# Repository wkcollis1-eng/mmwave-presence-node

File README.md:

<div align="center">

# mmWave Presence Lighting Node

**24 GHz Radar Presence Sensing for Room Lighting**

</div>

A 24 GHz radar presence sensor that turns a room's lamps on when someone walks in
and off some minutes after they leave — including for a person sitting still, in
the dark, reading, whom a PIR sensor cannot see.

An **HLK-LD2410C** radar and an **Adafruit VEML7700** light sensor on a **Seeed XIAO
ESP32-C3** carrier board, running **ESPHome**, with the control logic in **Home
Assistant**.

---

## The problem this is built for

> It is 23:00. The family room is dark and empty. A person walks in and sits down
> to read. The light comes on within one second, stays on for the next ninety
> minutes while they barely move, and goes off some minutes after they leave.
> Nobody touches a switch. Nobody is available to fix anything.

That is the acceptance test, not "99.9% uptime". A node that is powered and online
but drops the still-target at minute forty has failed the moment of demand — and so
has one that takes three seconds to notice someone walked in. The reasoning behind
every threshold, and the measurements that set them, are in
**[docs/mmwave-presence-node-design.md](docs/mmwave-presence-node-design.md)**.

## Status

| | |
|---|---|
| Design document | **Rev 1.11**, October 2026 |
| PCB | **Fabricated and populated.** 44.0 × 33.0 mm, 2-layer, three built |
| Bench validation | First session against real hardware **2026-09-07** — seven corrections and one retraction folded back into Rev 1.6. **14.5 days of bench data reviewed 2026-09-22** — folded into Rev 1.7 |
| Firmware / HA config | **Deployed.** Both nodes run firmware 0.4. The whole package (office and family room) is live in Home Assistant, derived from `packages/mmwave_presence.yaml` |
| Deployment | **Office live since 2026-09-26, family room since 2026-10-02.** First production review 2026-10-16, folded into Rev 1.8. A lamp lit into an empty room goes off after 5 min, from Rev 1.9 (2026-10-16). Family lamps the package lit go off on a bright morning, sunrise to noon, from Rev 1.10 (2026-10-19). Family lamps hold while the TV is on, from Rev 1.11 (2026-10-23) |
| Latency (R2) | **Family room: median 0.386 s, P95 0.409 s, n=103** [M] (HA's timestamps, presence edge → lamp relay on; not photons). **Office: median 2.404 s, P95 6.769 s, n=68** [M]. That is not met by design: the office lamp waits until the person is inside the approach limit, so a walk from the doorway is in the figure. Before that filter it was median 0.387 s, n=25 [M] — design doc §8 |
| Known fault | **The office node loses power every night**, about 23:30 to 07:00 [M: 13 nights, 09-29 → 10-12], and was dark for 79.66 h on 10-12 → 10-15 [M]. Under the §7 "lamp stays on while the node is offline" rule, the lamp stayed lit through 6 of those nights, 47.06 h in all [M]. Cause (owner, 2026-10-16): the node's outlet strip is fed by the Kasa computer outlet, which goes off overnight; the outlet's off-spans match all 14 dark gaps [M]. The remedy is the owner's call — design doc §9 item 16 |

The design document's §0 recorded what was its most consequential open question:
**the 5.6 m detection target and the gate-2 (7.4 ft) cap needed to reject a person
in the next room cannot both hold.** It is closed (owner-confirmed 2026-10-23), and
neither is kept for the office. The 5.6 m target is a family-room requirement only
(design doc §3.6); that node runs max gate 8. The office rejects the bathroom next
door in Home Assistant instead: occupancy starts only on a target reported inside
82 in (owner, 2026-10-16), live since 2026-09-27 as the P24 filter in
`packages/mmwave_presence.yaml`. A gate-2 cap was rejected because the doorway
reads at gate 3 too, so it would read a person standing there as empty. The office
radar still runs placeholder gates (move 4, still 4) until they are measured at the
mount (design doc §9 item 11).

## Repository layout

```
docs/          Design document, draft notes, the LD2410C documentation review,
               and the Hi-Link / Adafruit primary sources they cite
hardware/      KiCad 10 board, 3D models, gerbers, enclosure DXF, BOM
esphome/       Node firmware — common config plus per-node overlays
packages/      Home Assistant package: the control logic and its helpers
dashboards/    Home Assistant views for commissioning and monitoring
scripts/       Calibration and config-checking tools
assets/        Photos of the built node
```

`esphome/`, `packages/`, `dashboards/` and `scripts/` deliberately mirror the
layout under Home Assistant's `/config`, so a path named in the notes means the
same thing here and on the target.

## Hardware

| | |
|---|---|
| Board | 44.0 × 33.0 mm, 2-layer, 1 oz copper, 1.6 mm FR4 |
| Front copper | Pads and vias only, no traces — unbroken ground plane under the radar |
| Back copper | All routing. 1 mm power, 0.25 mm signal, 0.2 mm clearance |
| Mounting | 3 × M3 NPTH; H2 and H3 sit under U2's courtyard by design — use nylon fasteners |
| Vias | 67 total, 16 under the module, largest gap 5.39 mm (below λg = 5.96 mm) |

**1 oz / 1.6 mm, not 2 oz / 0.8 mm.** At 24.125 GHz the skin depth is 0.425 µm, so
1 oz is already 82 skin depths and 2 oz buys nothing electrically. 0.8 mm has 1/8
the flexural rigidity, which is the wrong direction for a vertically mounted board
carrying a cantilevered radar where flex changes the antenna-to-window distance.

### Radar interconnect

Module pin order, printed on the antenna face: **TX RX OUT GND VCC**.

| LD2410C | Signal | Direction | XIAO | GPIO |
|---|---|---|---|---|
| 1 | UART_Tx | module → ESP | D3 | GPIO5 |
| 2 | UART_Rx | ESP → module | D2 | GPIO4 |
| 3 | OUT | module → ESP | D10 | GPIO10 (via R1) |
| 4 | GND | — | GND | — |
| 5 | VCC | 5 V in | **VBUS**, not 3V3 | — |

> **Identify every pin by its silkscreen label, never by position or number.**
> VCC and TX sit at opposite ends of a five-pin header, so counting from the wrong
> end puts 5 V on TX. That is the one wiring error on this module that destroys
> something.

### PH1 — light sensor header

| pad | label | XIAO | GPIO |
|---|---|---|---|
| 1 | 3V3 (RED) | 3V3 | — |
| 2 | GND (BLACK) | GND | — |
| 3 | SCL (YELLOW) | D5 | GPIO7 |
| 4 | SDA (BLUE) | D4 | GPIO6 |

The colours match the Qwiic/STEMMA QT convention. **The pin order deliberately does
not** — it was chosen for cleaner routing, and the silkscreen colour labels are the
interface instead.

> ### Build constraint: only a flying-lead QT cable works
>
> Adafruit **4397** terminates in four independent female sockets, so each wire is
> placed by colour. **A molded 4-pin housing cable connects power backwards and
> destroys the sensor.** The board tells you the colours but not why.

**Cut the VEML7700's power-LED jumper before the sensor goes near the enclosure.**
The Adafruit 4162 carries a green power LED on the same face as the photodiode.
This is a sealed box: an ambient-light sensor locked in the dark with its own light
source is partly measuring that source, and because the offset is constant it
presents as a calibration rather than a fault.

**The light sensor is off-board on a 150 mm cable, by design.** On-carrier it sat
3.41 mm from the module edge — a near-field problem — and it could not be aimed
independently of the radar.

## Working on the board

Open `hardware/mmWave Presence Lighting Node.kicad_pro` in **KiCad 10**. All in-repo
3D models resolve through `${KIPRJMOD}/3d/`, so a fresh clone renders the full
assembly with no path fixing.

Two things to know before you file a bug against the board:

1. **There is no schematic.** The project is board-only, so KiCad cannot run
   connectivity or clearance DRC against a netlist — every error across seven
   revisions was found by reading coordinates. Building the schematic is open item
   §9.5 and is the one gate still running on human attention.
   *Corrected 2026-09-22: too strong. The pads carry net assignments, so DRC's
   connectivity check does run against the board's own nets — that is the
   "0 unconnected items" below. What is missing is an independent schematic to
   check those nets against.*
2. **`kicad-cli pcb drc` reports 16 violations, and that is the expected baseline** —
   3 errors, 13 warnings, 0 unconnected items. **Compare against this baseline
   rather than expecting zero.** It breaks down as:

   | n | severity | rule | why it is accepted |
   |---|---|---|---|
   | 2 | error | `courtyards_overlap` | H2 and H3 sit under U2's courtyard **by design** — see §3.1 and the nylon-fastener note in §3.9 |
   | 1 | error | `npth_inside_courtyard` | same cause: a mounting hole inside the module's courtyard |
   | 4 | warning | `silk_over_copper` | cosmetic, reviewed |
   | 2 | warning | `silk_edge_clearance` | cosmetic, reviewed |
   | 6 | warning | `lib_footprint_mismatch` | stock footprints deliberately modified in place (C1 relocated for U.FL clearance, 3D models attached) |
   | 1 | warning | `lib_footprint_issues` | U2 — its footprint is stored inline in the board with no library behind it |

## Third-party assets

Full detail, including the terms that apply to each, is in
**[THIRD_PARTY_NOTICES.md](THIRD_PARTY_NOTICES.md)**. These files are *not*
covered by this repository's own licences.

> **One file is non-commercial.** The LD2410C radar mesh
> (`hardware/3d/LD2410C mmWave Sensor.step` and its snapshot directory) is
> CC BY-NC 4.0. It is a 3D viewer mesh only — it is not in the gerbers, so it
> does not restrict manufacturing this board. For commercial use, delete those
> paths and render U2 with the Hi-Link model instead.

| Asset | Origin | Note |
|---|---|---|
| `hardware/3d/LD2410C mmWave Sensor.step` | Ben Cooney, via [GrabCAD](https://grabcad.com/library/ld2410c-mmwave-sensor-1) | **CC BY-NC 4.0** — non-commercial; licence image ships in `ld2410c-mmwave-sensor-1.snapshot.2/` |
| `hardware/3d/HLK-LD2410C-3D图/` | Hi-Link | Manufacturer 3D model |
| `hardware/3d/Adafruit VEML7700.zip` | SnapMagic | Part models remain SnapMagic's intellectual property |
| `docs/LD2410C Docs/*.pdf` | Hi-Link, Adafruit | Datasheet, serial protocol V1.07, VEML7700 guide |
| `hardware/3d/Seeed-Studio-XIAO-ESP32-C3.step` | Seeed Studio | |

Where the Hi-Link datasheet and the serial protocol document disagree, the protocol
document wins: it is two years newer and it documents the commands the module obeys.

## Credentials

Every credential in this repository resolves through ESPHome `!secret`, and the
`secrets.yaml` those resolve against lives in the Home Assistant config, **not
here**. Git history has been scanned and contains no plaintext SSID, PSK, API
encryption key or OTA password in any commit.

---

## License

Three licences, because this repository holds three different kinds of work:

| Content | Paths | Licence |
|---|---|---|
| Hardware design | `hardware/` | [CERN-OHL-S v2](LICENSE-HARDWARE) |
| Code | `esphome/`, `packages/`, `dashboards/`, `scripts/` | [MIT](LICENSE-CODE) |
| Documentation | `docs/`, this README | [CC BY 4.0](https://creativecommons.org/licenses/by/4.0/) |

See **[LICENSE](LICENSE)** for the full breakdown and attribution examples, and
**[THIRD_PARTY_NOTICES.md](THIRD_PARTY_NOTICES.md)** for the vendor files that
none of the above covers.

CERN-OHL-S is strongly reciprocal: build the board, sell it, modify it — but if
you convey a modified design or a product made from it, the modified source has
to be available under the same terms.

```
Copyright (C) 2026 William K. Collis

This source describes Open Hardware and is licensed under the CERN-OHL-S v2.

You may redistribute and modify this source and make products using it under
the terms of the CERN-OHL-S v2 (https://ohwr.org/cern_ohl_s_v2.txt).

This source is distributed WITHOUT ANY EXPRESS OR IMPLIED WARRANTY, INCLUDING
OF MERCHANTABILITY, SATISFACTORY QUALITY AND FITNESS FOR A PARTICULAR PURPOSE.
Please see the CERN-OHL-S v2 for applicable conditions.

Source location: https://github.com/wkcollis1-eng/mmwave-presence-node
```

---

## 💝 Support This Project

If this design document or the commissioning method saved you time on your own
presence-sensing build, sponsorship funds continued instrumentation, hardware
and documentation.

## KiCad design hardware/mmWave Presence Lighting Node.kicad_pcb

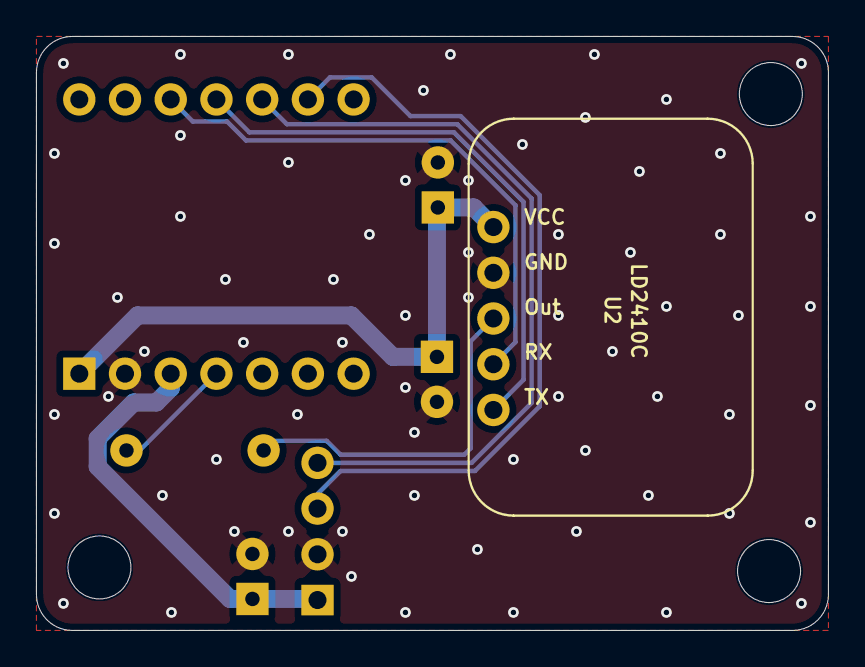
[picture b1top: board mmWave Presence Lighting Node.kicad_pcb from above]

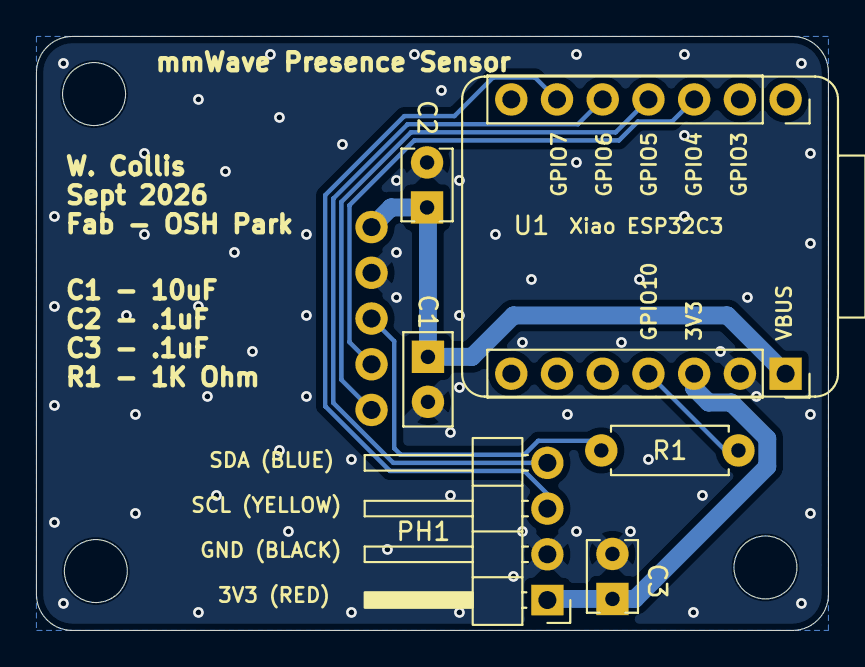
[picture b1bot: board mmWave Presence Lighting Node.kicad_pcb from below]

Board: 2 copper layers, 44.0 x 33.0 mm, 10 parts (6 on the bottom side), 9 nets.

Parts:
C1: C_Disc_D5.0mm_W2.5mm_P2.50mm
C2, C3: C_Disc_D3.8mm_W2.6mm_P2.50mm
H1, H2, H3: MountingHole_3.5mm
PH1: PinHeader_1x04_P2.54mm_Horizontal
R1: R_Axial_DIN0207_L6.3mm_D2.5mm_P7.62mm_Horizontal
U1: SeeedStudio_XIAO_ESP32C3
U2: LD2410C Sensor Module; SeeedStudio_24gHz_mmWave

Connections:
3.3V: C3.2, PH1.1, U1.3V3
GND: C1.2, C2.1, C3.1, PH1.2, U1.GND, U2.2
Radar_MCU: R1.1, U1.10
Radar_Out: R1.2, U2.3
Radar_RX: U1.2, U2.4
Radar_TX: U1.3, U2.5
SCL: PH1.3, U1.5
SDA: PH1.4, U1.4
VBUS: C1.1, C2.2, U1.VBUS, U2.1

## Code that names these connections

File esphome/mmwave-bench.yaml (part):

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  board_type: seeed_xiao_esp32c3

  # ---- PINS (raw GPIO — see the wiring table above) ------------------------
  pin_radar_tx: GPIO4     # XIAO D2  -> module RX
  pin_radar_rx: GPIO5     # XIAO D3  <- module TX
  pin_radar_out: GPIO10   # XIAO D10 <- module OUT

  # ---- THE LAMP (added 2026-09-07) ----------------------------------------
  # §7 option 2: "move the decision to the ESP driving a smart relay with HA
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
uart:
  id: uart_radar
  tx_pin: ${pin_radar_tx}
  rx_pin: ${pin_radar_rx}
  baud_rate: ${radar_baud}
  parity: NONE
  stop_bits: 1
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  # and the obvious "fix" of overriding it would only reintroduce flooding.
  - platform: gpio
    pin:
      number: ${pin_radar_out}
      mode:
        input: true
        # NO pull-up and NO pull-down. OUT is push-pull — it drives both rails
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

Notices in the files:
README.md:
Docs: CC BY 4.0
